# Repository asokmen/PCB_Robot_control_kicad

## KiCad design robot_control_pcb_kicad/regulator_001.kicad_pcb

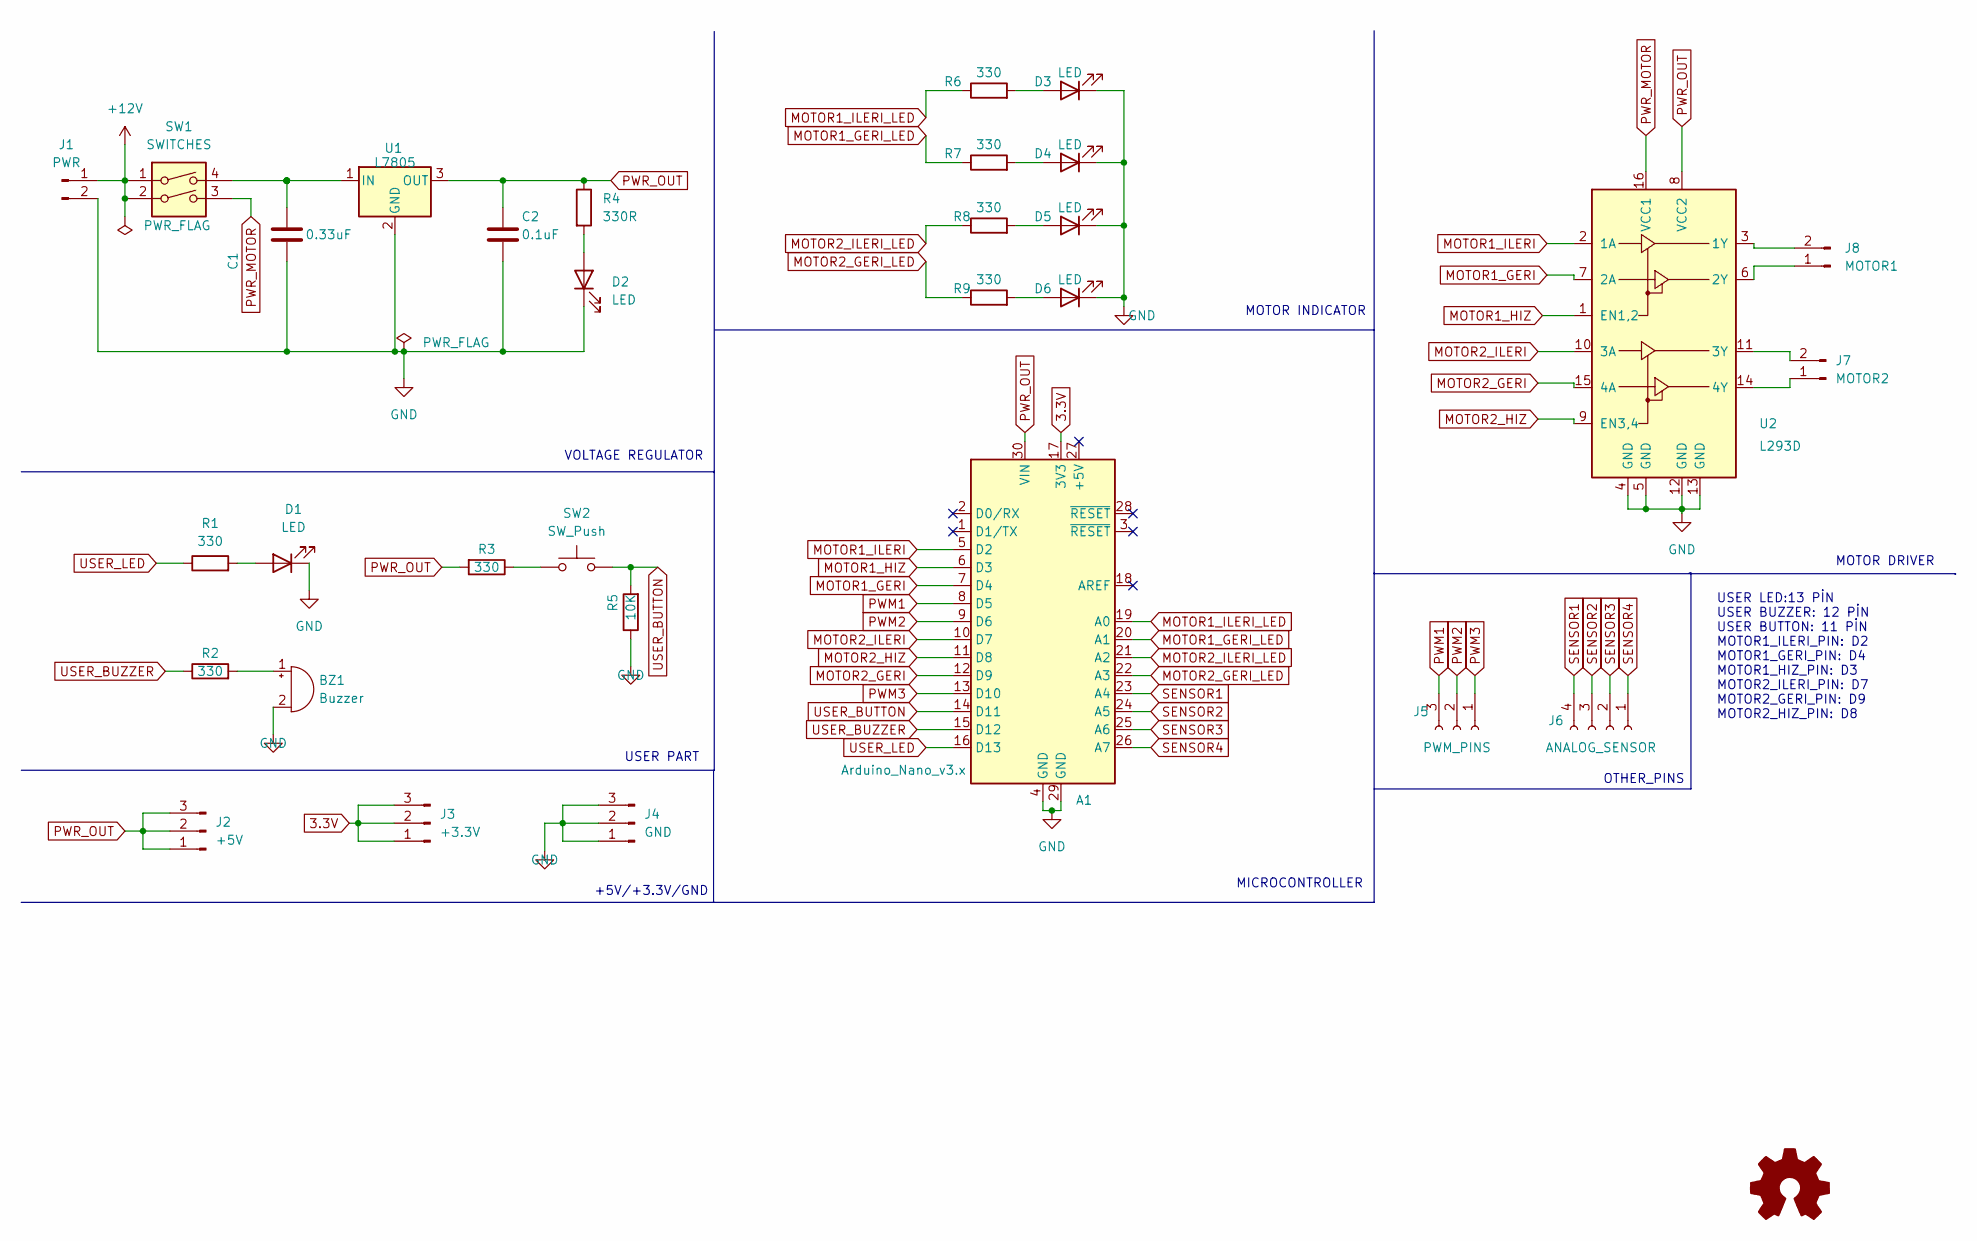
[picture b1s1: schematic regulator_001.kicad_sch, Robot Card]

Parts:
A1: Arduino_Nano_v3.x; Arduino_Nano
BZ1: Buzzer; Buzzer_12x9.5RM7.6
C1: 0.33uF; C_Disc_D3.0mm_W2.0mm_P2.50mm
C2: 0.1uF; C_Disc_D3.0mm_W2.0mm_P2.50mm
D1, D2, D3, D4, D5, D6: LED; LED_D3.0mm
J1: PWR; Molex_KK-254_AE-6410-02A_1x02_P2.54mm_Vertical
J2: +5V; PinHeader_1x03_P2.54mm_Vertical
J3: +3.3V; PinHeader_1x03_P2.54mm_Vertical
J4: GND; PinHeader_1x03_P2.54mm_Vertical
J5: PWM_PINS; PinSocket_1x03_P2.54mm_Vertical
J6: ANALOG_SENSOR; PinSocket_1x04_P2.54mm_Vertical
J7: MOTOR2; Molex_KK-254_AE-6410-02A_1x02_P2.54mm_Vertical
J8: MOTOR1; Molex_KK-254_AE-6410-02A_1x02_P2.54mm_Vertical
R1, R2, R3, R6, R7, R8, R9: 330; R_Axial_DIN0204_L3.6mm_D1.6mm_P5.08mm_Horizontal
R4: 330R; R_Axial_DIN0204_L3.6mm_D1.6mm_P5.08mm_Horizontal
R5: 10K; R_Axial_DIN0204_L3.6mm_D1.6mm_P5.08mm_Horizontal
SW1: SWITCHES; SW_DIP_SPSTx02_Slide_6.7x6.64mm_W7.62mm_P2.54mm_LowProfile
SW2: SW_Push; SW_PUSH_6mm_H4.3mm
U1: L7805; TO-220-3_Vertical
U2: L293D; DIP-16_W7.62mm

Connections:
3.3V: A1.17 (3V3), J3.1, J3.2, J3.3
+12V: J1.1, SW1.1, SW1.2
GND: A1.4 (GND), A1.29 (GND), BZ1.2 (+), C1.2, C2.2, D1.1 (K), D2.1 (K), D3.1 (K), D4.1 (K), D5.1 (K), D6.1 (K), J1.2, J4.1, J4.2, J4.3, R5.1, U1.2 (GND), U2.4 (GND), U2.5 (GND), U2.12 (GND), U2.13 (GND)
MOTOR1_GERI: A1.7 (D4), U2.7 (2A)
MOTOR1_GERI_LED: A1.20 (A1), R7.1
MOTOR1_HIZ: A1.6 (D3), U2.1 (EN1,2)
MOTOR1_ILERI: A1.5 (D2), U2.2 (1A)
MOTOR1_ILERI_LED: A1.19 (A0), R6.1
MOTOR2_GERI: A1.12 (D9), U2.15 (4A)
MOTOR2_GERI_LED: A1.22 (A3), R9.1
MOTOR2_HIZ: A1.11 (D8), U2.9 (EN3,4)
MOTOR2_ILERI: A1.10 (D7), U2.10 (3A)
MOTOR2_ILERI_LED: A1.21 (A2), R8.1
unnamed: BZ1.1 (-), R2.2
unnamed: C1.1, SW1.4, U1.1 (IN)
unnamed: D1.2 (A), R1.2
unnamed: D2.2 (A), R4.2
unnamed: D3.2 (A), R6.2
unnamed: D4.2 (A), R7.2
unnamed: D5.2 (A), R8.2
unnamed: D6.2 (A), R9.2
unnamed: J7.1, U2.14 (4Y)
unnamed: J7.2, U2.11 (3Y)
unnamed: J8.1, U2.6 (2Y)
unnamed: J8.2, U2.3 (1Y)
unnamed: R3.1, SW2.1
PWM1: A1.8 (D5), J5.3
PWM2: A1.9 (D6), J5.2
PWM3: A1.13 (D10), J5.1
PWR_MOTOR: SW1.3, U2.16 (VCC1)
PWR_OUT: A1.30 (VIN), C2.1, J2.1, J2.2, J2.3, R3.2, R4.1, U1.3 (OUT), U2.8 (VCC2)
SENSOR1: A1.23 (A4), J6.4
SENSOR2: A1.24 (A5), J6.3
SENSOR3: A1.25 (A6), J6.2
SENSOR4: A1.26 (A7), J6.1
USER_BUTTON: A1.14 (D11), R5.2, SW2.2
USER_BUZZER: A1.15 (D12), R2.1
USER_LED: A1.16 (D13), R1.1

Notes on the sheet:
MOTOR DRIVER
MOTOR INDICATOR
USER LED:13 PİN USER BUZZER: 12 PİN USER BUTTON: 11 PİN MOTOR1_ILERI_PIN: D2 MOTOR1_GERI_PIN: D4 MOTOR1_HIZ_PIN: D3 MOTOR2_ILERI_PIN: D7 MOTOR2_GERI_PIN: D9 MOTOR2_HIZ_PIN: D8
MICROCONTROLLER
OTHER_PINS
USER PART
+5V/+3.3V/GND
VOLTAGE REGULATOR

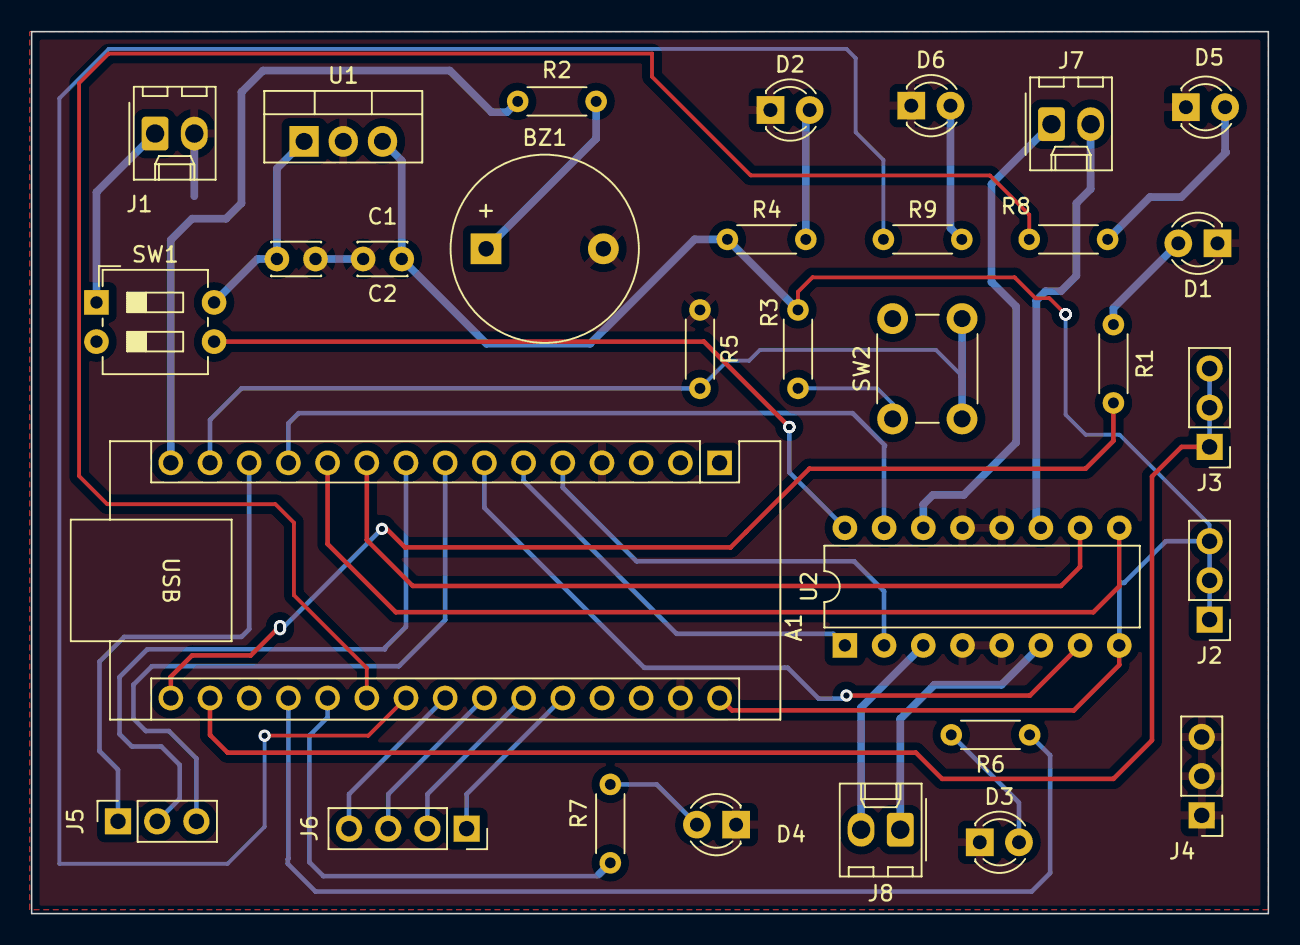
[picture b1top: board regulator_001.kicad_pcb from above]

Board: 2 copper layers, 80.1 x 57.1 mm, 31 parts (0 on the bottom side), 38 nets.
